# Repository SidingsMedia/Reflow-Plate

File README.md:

<!-- 
SPDX-FileCopyrightText: Copyright (c) 2021-2022 Sidings Media 

SPDX-License-Identifier: MIT
-->
# Reflow Plate

This repo contains the schematics, board designs and firmware for
Sidings Media's version of the PCB based SMD reflow plate. The reflow
plate provides a convenient way to easily reflow PCBs cheaply. Thanks to
[AfterEarthLTD](https://github.com/AfterEarthLTD/Solder-Reflow-Plate)
for the original inspiration. This version aims to provide greater
modulatity to the system allowing for a range of different board sizes
and micro controller boards to be used. 

## Licence
This repo uses the [REUSE](https://reuse.software) standard in order to communicate the correct licence for the file. For those unfamiliar with the standard the licence for each file can be found in one of three places. The licence will either be in a comment block at the top of the file, in a `.license` file with the same name as the file, or in the dep5 file located in the `.reuse` directory. If you are unsure of the licencing terms please contact [contact@sidingsmedia.com](mailto:contact@sidingsmedia.com). All files committed to this repo must contain valid licencing information or the pull request can not be accepted.

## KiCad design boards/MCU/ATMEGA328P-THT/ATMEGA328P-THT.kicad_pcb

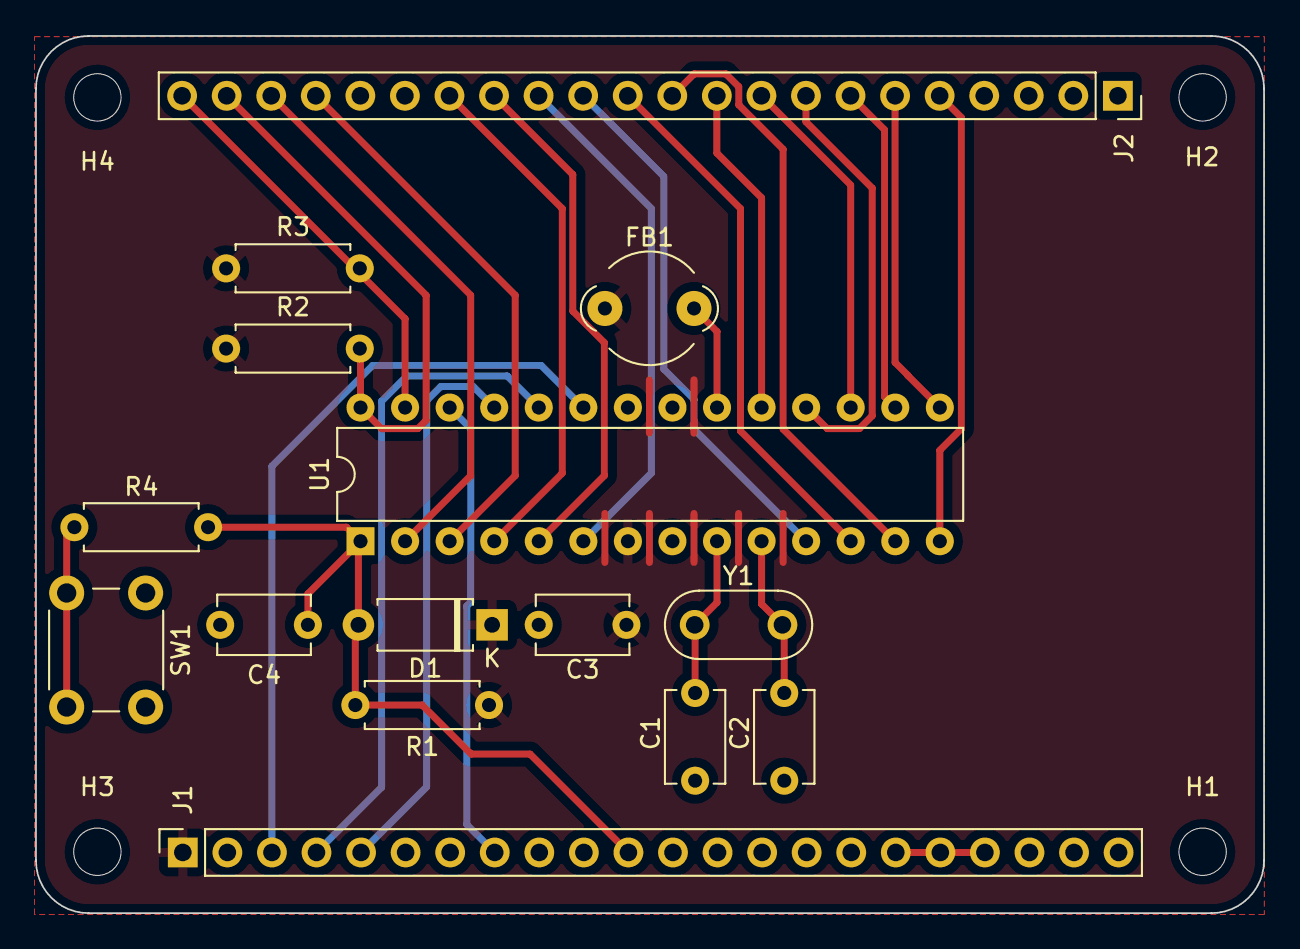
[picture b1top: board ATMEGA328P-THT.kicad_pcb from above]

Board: 2 copper layers, 70.0 x 50.0 mm, 19 parts (0 on the bottom side), 28 nets.

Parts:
C1, C2: 27pF; C_Disc_D5.1mm_W3.2mm_P5.00mm
C3: 100nF; C_Disc_D5.1mm_W3.2mm_P5.00mm
C4: 10nF; C_Disc_D5.1mm_W3.2mm_P5.00mm
D1: 1N4001; D_A-405_P7.62mm_Horizontal
FB1: FerriteBead; LairdTech_28C0236-0JW-10
H1, H2, H3, H4: MountingHole; MountingHole_2.7mm_M2.5
J1, J2: Conn_01x22_Female; PinSocket_1x22_P2.54mm_Vertical
R1, R2, R3: 10K; R_Axial_DIN0207_L6.3mm_D2.5mm_P7.62mm_Horizontal
R4: 330R; R_Axial_DIN0207_L6.3mm_D2.5mm_P7.62mm_Horizontal
SW1: SW_Push; SW_PUSH_6mm
U1: ATmega328-P; DIP-28_W7.62mm
Y1: 16MHz; Resonator-2Pin_W8.0mm_H3.5mm

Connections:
+5V: C3.1, D1.1 (K), FB1.1, J1.1, R1.1, R2.1, R3.1, U1.7 (VCC)
+12V: J1.17, J1.18, J1.19
/CURRENT_SENSE_A: J1.8, U1.26 (PC3)
/GPIO0: J2.16, U1.4 (PD2)
/GPIO1: J2.15, U1.5 (PD3)
/GPIO2: J2.14, U1.6 (PD4)
/GPIO3: J2.13, U1.11 (PD5)
/GPIO4: J2.12, U1.12 (PD6)
/GPIO5: J2.11, U1.13 (PD7)
/MISO: J2.8, U1.18 (PB4)
/MOSI: J2.9, U1.17 (PB3)
/Rx0: J2.19, U1.3 (PD1)
/SCL: J2.21, R2.2, U1.28 (PC5)
/SCLK: J2.10, U1.19 (PB5)
/SDA: J2.22, R3.2, U1.27 (PC4)
/TEMP_SENSE_A: J1.3, U1.23 (PC0)
/TEMP_SENSE_B: J1.4, U1.24 (PC1)
/TEMP_SENSE_C: J1.5, U1.25 (PC2)
/Tx0: J2.20, U1.2 (PD0)
/XTAL1: C1.1, U1.9 (XTAL1/PB6), Y1.1
/XTAL2: C2.1, U1.10 (XTAL2/PB7), Y1.2
/~RESET: C4.1, D1.2 (A), J1.11, R1.2, R4.1, U1.1 (~RESET/PC6)
/~SS1: J2.7, U1.16 (PB2)
/~SS2: J2.6, U1.15 (PB1)
/~SS3: J2.5, U1.14 (PB0)
GND: C1.2, C2.2, C3.2, C4.2, J1.20, J1.21, J1.22, J2.1, J2.2, SW1.1, U1.8 (GND), U1.22 (GND)
unnamed: R4.2, SW1.2
unnamed: FB1.2, U1.20 (AVCC)

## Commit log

2022-04-10 Updated template to match project
2022-04-10 Added basic RP2040 kicad project
2022-04-10 Added basic docs structure
2022-04-10 Fixed config for docs
2022-04-10 Added overview of boards
2022-05-25 Added basic docs
2022-05-25 Fixed formatting for diagram
2022-05-25 Fixed TOC tree
2022-05-25 Updated pin assignments
2022-05-25 Fixed indentation of code-block
2022-05-25 Removed old files
2022-05-25 Added basic ATMEGA328P connections
2022-05-26 Changed from 24 to 22 pin connectors
2022-05-26 Added mechanical spec
2022-05-26 Fixed image path
2022-05-26 Added reset pin
2022-05-26 Added ATMEGA328P THT MCU board
